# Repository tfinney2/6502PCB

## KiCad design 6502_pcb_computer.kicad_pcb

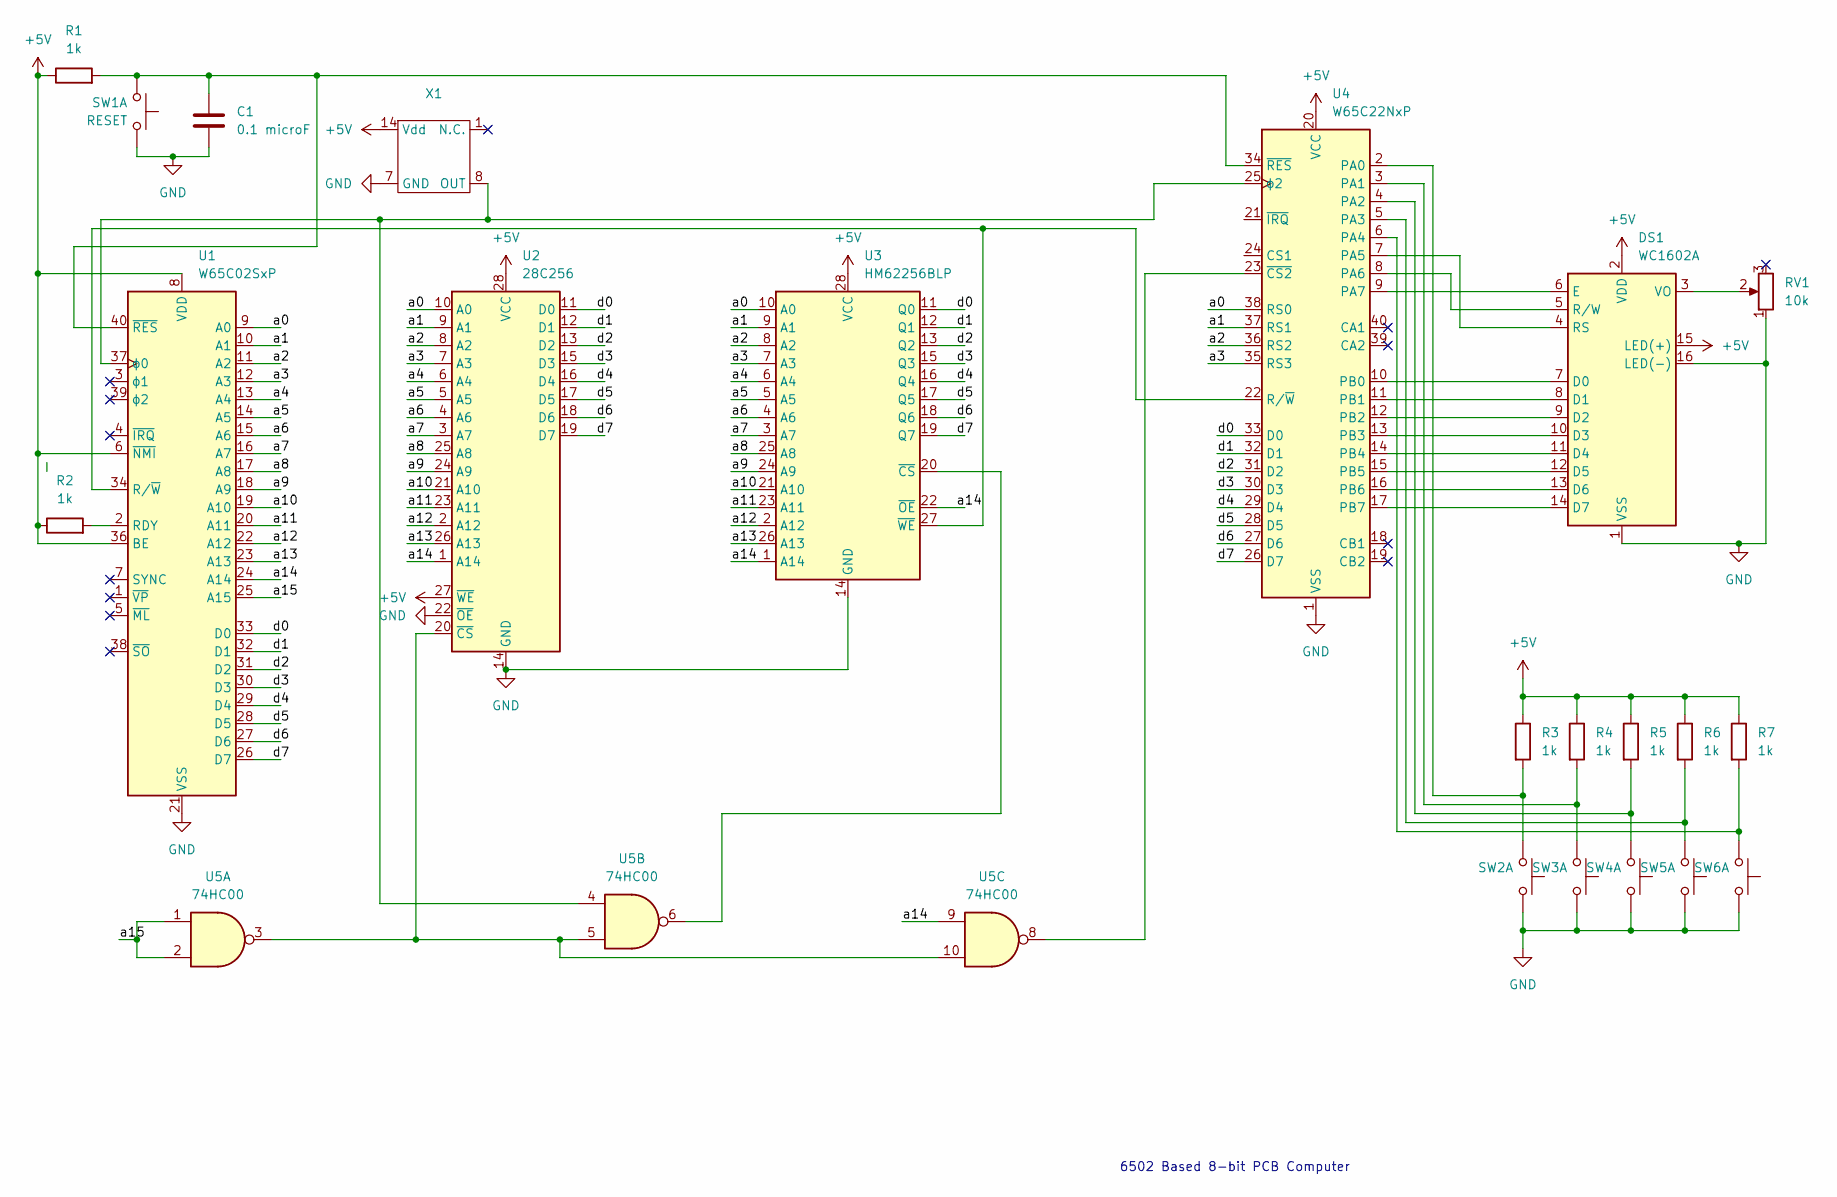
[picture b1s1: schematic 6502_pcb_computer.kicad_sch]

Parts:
C1: 0.1 microF; C_Disc_D3.0mm_W2.0mm_P2.50mm
DS1: WC1602A
R1, R2, R3, R4, R5, R6, R7: 1k; R_Axial_DIN0207_L6.3mm_D2.5mm_P7.62mm_Horizontal
RV1: 10k; Potentiometer_Bourns_3386W_Horizontal
SW1: RESET; SW_PUSH_1P1T_6x3.5mm_H5.0_APEM_MJTP1250
SW2, SW3, SW4, SW5, SW6: SW_PUSH_1P1T_6x3.5mm_H5.0_APEM_MJTP1250
U1: W65C02SxP; DIP-40_W15.24mm
U2: 28C256; DIP-28_W15.24mm_Socket_LongPads
U3: HM62256BLP; DIP-28_W15.24mm
U4: W65C22NxP; DIP-40_W15.24mm
U5: 74HC00; CERDIP-14_W7.62mm_SideBrazed
X1: MCO-1510A

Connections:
+5V: DS1.2 (VDD), DS1.15 (LED(+)), R1.1, R2.1, R3.1, R4.1, R5.1, R6.1, R7.1, U1.6 (~NMI), U1.8 (VDD), U1.36 (BE), U2.27 (~WE), U2.28 (VCC), U3.28 (VCC), U4.20 (VCC), X1.14 (Vdd)
/a0: U1.9 (A0), U2.10 (A0), U3.10 (A0), U4.38 (RS0)
/a1: U1.10 (A1), U2.9 (A1), U3.9 (A1), U4.37 (RS1)
/a2: U1.11 (A2), U2.8 (A2), U3.8 (A2), U4.36 (RS2)
/a3: U1.12 (A3), U2.7 (A3), U3.7 (A3), U4.35 (RS3)
/a4: U1.13 (A4), U2.6 (A4), U3.6 (A4)
/a5: U1.14 (A5), U2.5 (A5), U3.5 (A5)
/a6: U1.15 (A6), U2.4 (A6), U3.4 (A6)
/a7: U1.16 (A7), U2.3 (A7), U3.3 (A7)
/a8: U1.17 (A8), U2.25 (A8), U3.25 (A8)
/a9: U1.18 (A9), U2.24 (A9), U3.24 (A9)
/a10: U1.19 (A10), U2.21 (A10), U3.21 (A10)
/a11: U1.20 (A11), U2.23 (A11), U3.23 (A11)
/a12: U1.22 (A12), U2.2 (A12), U3.2 (A12)
/a13: U1.23 (A13), U2.26 (A13), U3.26 (A13)
/a14: U1.24 (A14), U2.1 (A14), U3.1 (A14), U3.22 (~OE), U5.9
/a15: U1.25 (A15), U5.1, U5.2
/d0: U1.33 (D0), U2.11 (D0), U3.11 (Q0), U4.33 (D0)
/d1: U1.32 (D1), U2.12 (D1), U3.12 (Q1), U4.32 (D1)
/d2: U1.31 (D2), U2.13 (D2), U3.13 (Q2), U4.31 (D2)
/d3: U1.30 (D3), U2.15 (D3), U3.15 (Q3), U4.30 (D3)
/d4: U1.29 (D4), U2.16 (D4), U3.16 (Q4), U4.29 (D4)
/d5: U1.28 (D5), U2.17 (D5), U3.17 (Q5), U4.28 (D5)
/d6: U1.27 (D6), U2.18 (D6), U3.18 (Q6), U4.27 (D6)
/d7: U1.26 (D7), U2.19 (D7), U3.19 (Q7), U4.26 (D7)
GND: C1.2, DS1.1 (VSS), DS1.16 (LED(-)), RV1.1, SW1.1 (C), SW2.1 (C), SW3.1 (C), SW4.1 (C), SW5.1 (C), SW6.1 (C), U1.21 (VSS), U2.14 (GND), U2.22 (~OE), U3.14 (GND), U4.1 (VSS), X1.7 (GND)
unnamed: DS1.7 (D0), U4.10 (PB0)
unnamed: DS1.8 (D1), U4.11 (PB1)
unnamed: DS1.9 (D2), U4.12 (PB2)
unnamed: DS1.10 (D3), U4.13 (PB3)
unnamed: DS1.11 (D4), U4.14 (PB4)
unnamed: DS1.12 (D5), U4.15 (PB5)
unnamed: DS1.13 (D6), U4.16 (PB6)
unnamed: DS1.14 (D7), U4.17 (PB7)
unnamed: DS1.6 (E), U4.9 (PA7)
unnamed: DS1.4 (RS), U4.7 (PA5)
unnamed: DS1.5 (R/W), U4.8 (PA6)
unnamed: DS1.3 (VO), RV1.2
unnamed: C1.1, R1.2, SW1.2 (D), U1.40 (~RES), U4.34 (~RES)
unnamed: R3.2, SW2.2 (D), U4.2 (PA0)
unnamed: R4.2, SW3.2 (D), U4.3 (PA1)
unnamed: R5.2, SW4.2 (D), U4.4 (PA2)
unnamed: R6.2, SW5.2 (D), U4.5 (PA3)
unnamed: R7.2, SW6.2 (D), U4.6 (PA4)
unnamed: R2.2, U1.2 (RDY)
unnamed: U1.34 (R/~W), U3.27 (~WE), U4.22 (R/~W)
unnamed: U1.37 (ϕ0), U4.25 (ϕ2), U5.4, X1.8 (OUT)
unnamed: U2.20 (~CS), U5.3, U5.5, U5.10
unnamed: U3.20 (~CS), U5.6
unnamed: U4.23 (~CS2), U5.8

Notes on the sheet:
6502 Based 8-bit PCB Computer

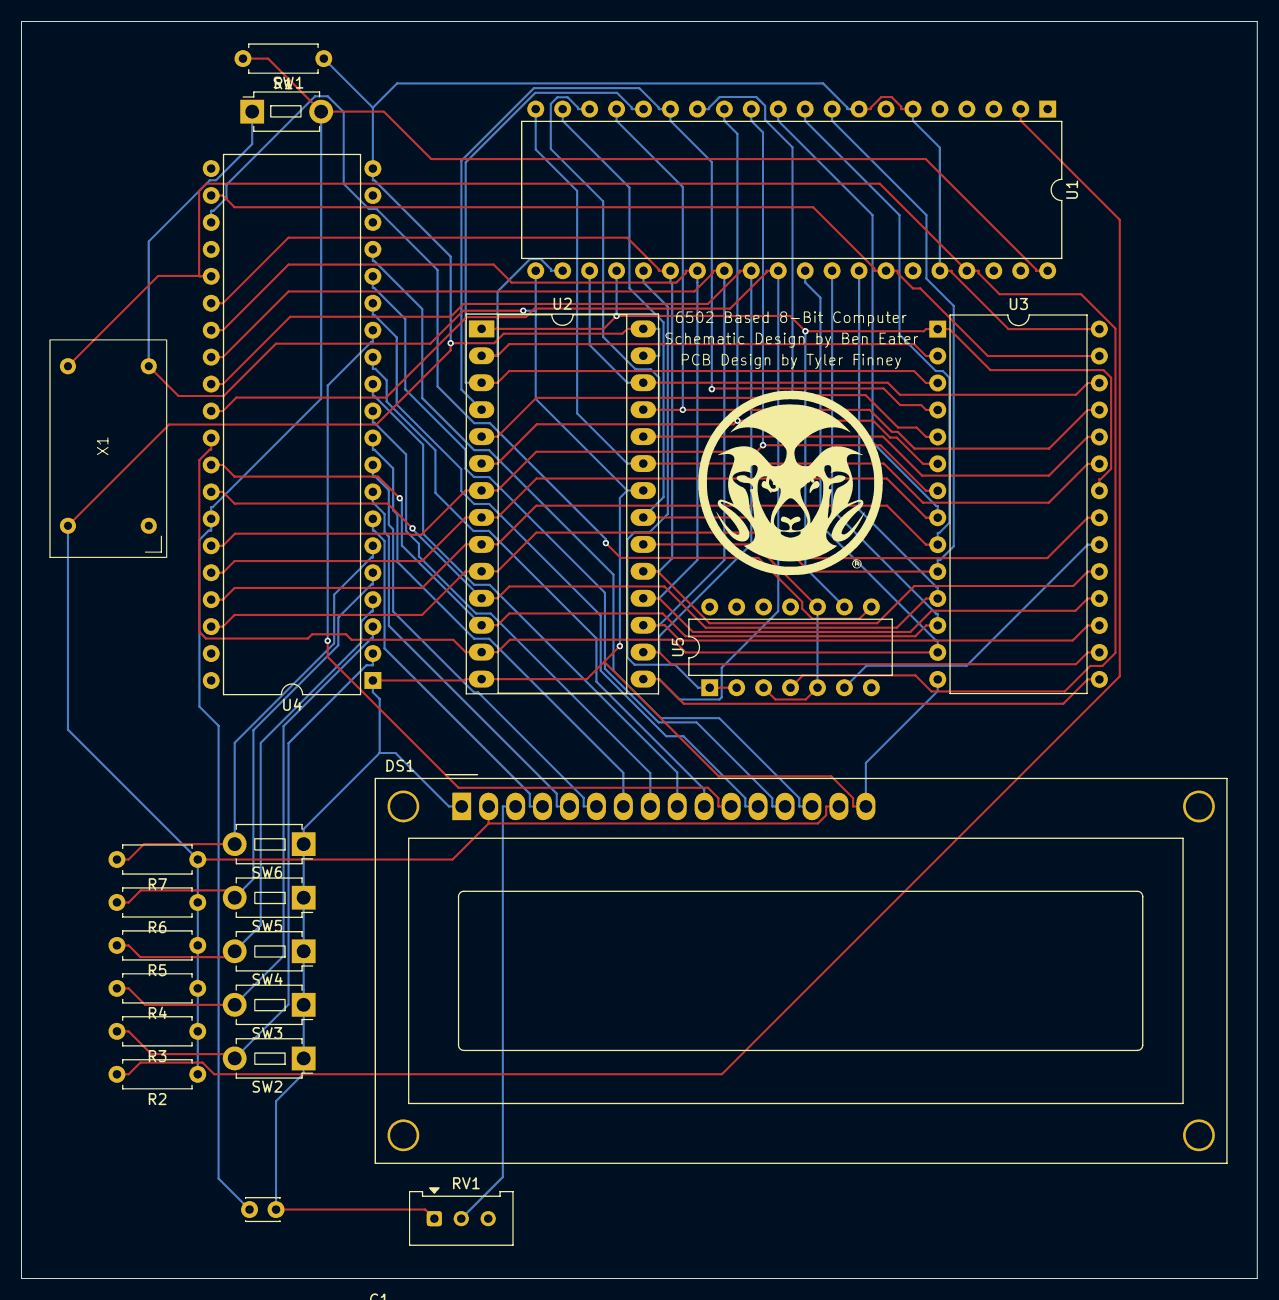
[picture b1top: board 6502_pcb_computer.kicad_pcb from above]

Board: 2 copper layers, 116.5 x 118.5 mm, 22 parts (0 on the bottom side), 50 nets.
